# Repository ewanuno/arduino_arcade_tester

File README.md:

this is a simple arduino project to test arcade redemption ticket dispensers and coin acceptors

its been designed to work with Tong li animation tw-950 coin acceptors and TL-002IV ticket distributors.

it should work with others, but if they use 12v signals then it will probably cook your arduino. 

Max vibe coded it and i helped him to get it working and designed the PCB

the lcd is a generic 1602iic

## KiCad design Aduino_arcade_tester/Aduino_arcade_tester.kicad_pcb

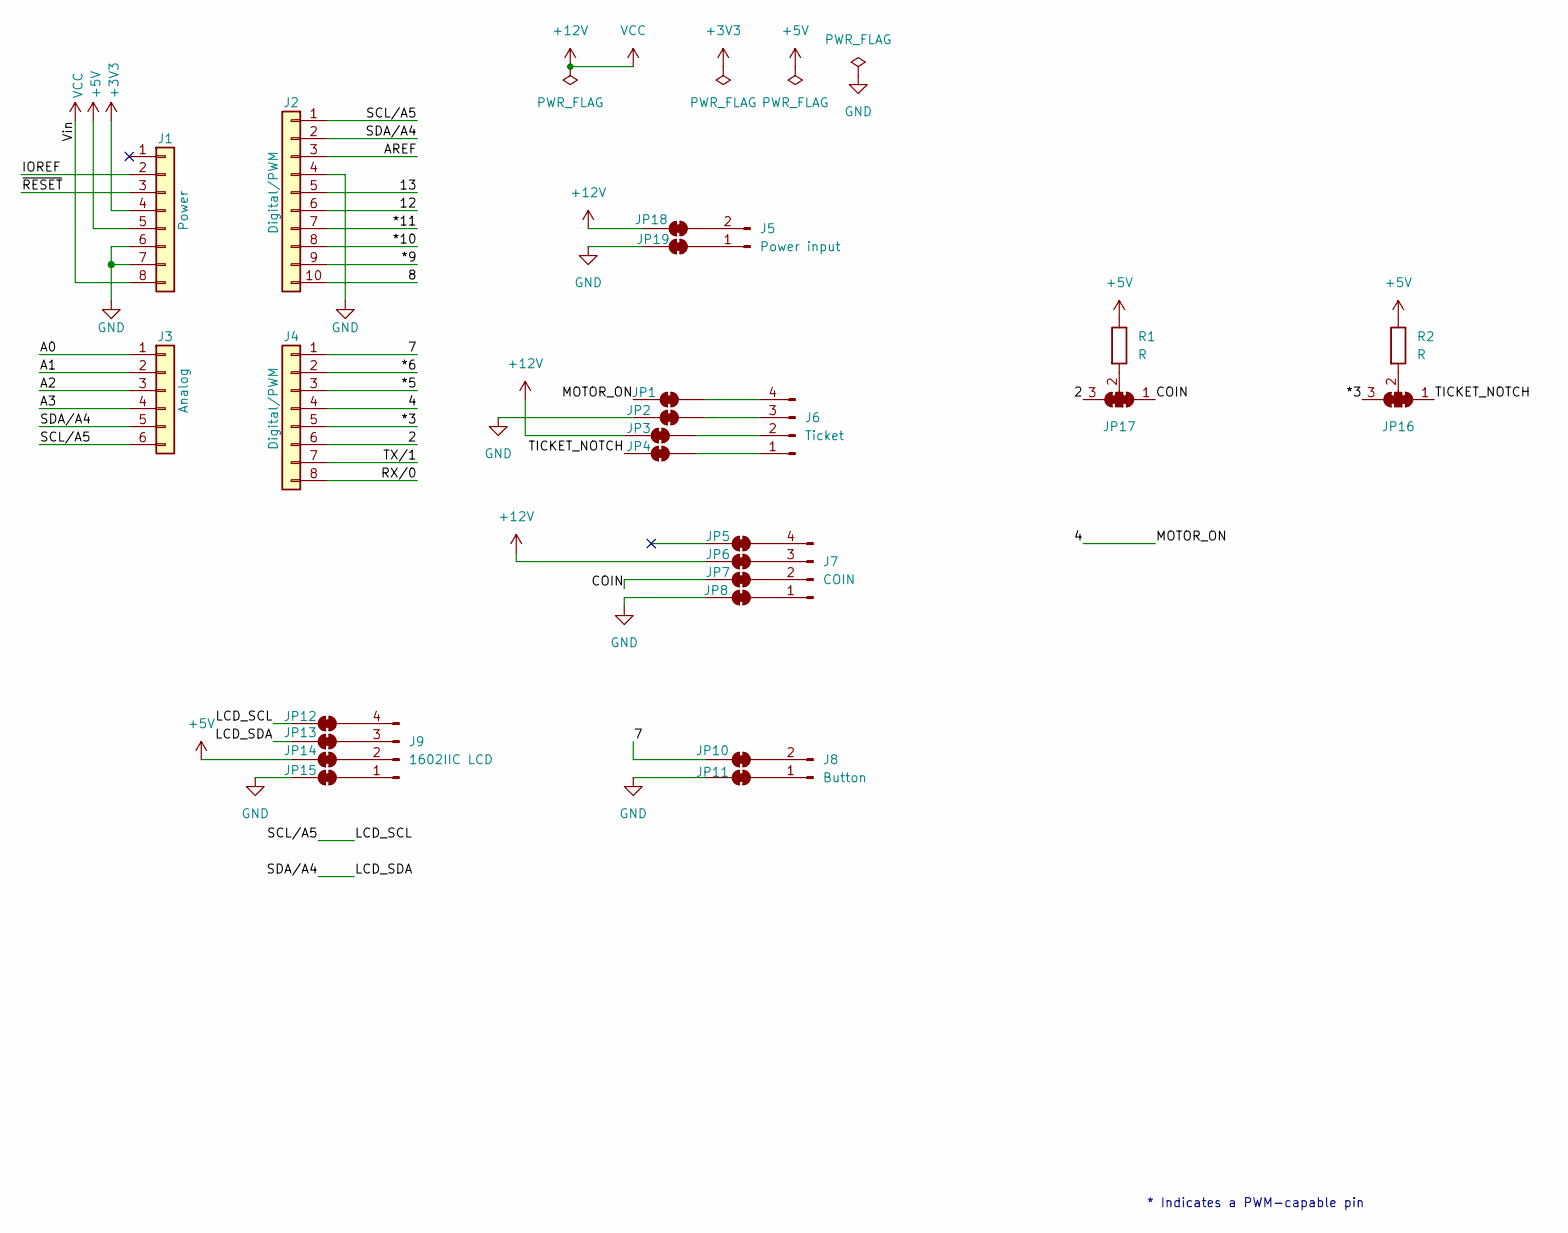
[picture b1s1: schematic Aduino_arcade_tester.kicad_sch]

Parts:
J1: Power; PinSocket_1x08_P2.54mm_Vertical
J2: Digital/PWM; PinSocket_1x10_P2.54mm_Vertical
J3: Analog; PinSocket_1x06_P2.54mm_Vertical
J4: Digital/PWM; PinSocket_1x08_P2.54mm_Vertical
J5: Power input; TerminalBlock_Phoenix_MKDS-1,5-2_1x02_P5.00mm_Horizontal
J6: Ticket; TerminalBlock_Phoenix_MKDS-1,5-4_1x04_P5.00mm_Horizontal
J7: COIN; TerminalBlock_Phoenix_MKDS-1,5-4_1x04_P5.00mm_Horizontal
J8: Button; TerminalBlock_Phoenix_MKDS-1,5-2_1x02_P5.00mm_Horizontal
J9: 1602IIC LCD; PinHeader_1x04_P2.54mm_Vertical
JP1, JP2, JP3, JP4, JP5, JP6, JP7, JP8, JP10, JP11, JP12, JP13, JP14, JP15, JP18, JP19: SolderJumper_2_Bridged; SolderJumper-2_P1.3mm_Bridged_RoundedPad1.0x1.5mm
JP16, JP17: SolderJumper_3_Bridged123; SolderJumper-3_P1.3mm_Bridged123_RoundedPad1.0x1.5mm_Number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
R1, R2: R; R_Axial_DIN0204_L3.6mm_D1.6mm_P5.08mm_Horizontal

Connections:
+3V3: J1.4
+5V: J1.5, JP14.1 (A), R1.1, R2.1
+12V: J1.8, JP3.1 (A), JP6.1 (A), JP18.1 (A)
/2: J4.6, JP17.3 (B)
/4: J4.4, JP1.1 (A)
/7: J4.1, JP10.1 (A)
/8: J2.10
/12: J2.6
/13: J2.5
/*3: J4.5, JP16.3 (B)
/*5: J4.3
/*6: J4.2
/*9: J2.9
/*10: J2.8
/*11: J2.7
/A0: J3.1
/A1: J3.2
/A2: J3.3
/A3: J3.4
/AREF: J2.3
/COIN: JP7.1 (A), JP17.1 (A)
/IOREF: J1.2
/LCD_SCL: J2.1, J3.6, JP12.1 (A)
/LCD_SDA: J2.2, J3.5, JP13.1 (A)
/RX/0: J4.8
/TICKET_NOTCH: JP4.1 (A), JP16.1 (A)
/TX/1: J4.7
/~RESET: J1.3
GND: J1.6, J1.7, J2.4, JP2.1 (A), JP8.1 (A), JP11.1 (A), JP15.1 (A), JP19.1 (A)
unnamed: J5.1, JP19.2 (B)
unnamed: J5.2, JP18.2 (B)
unnamed: J6.1, JP4.2 (B)
unnamed: J6.2, JP3.2 (B)
unnamed: J6.3, JP2.2 (B)
unnamed: J6.4, JP1.2 (B)
unnamed: J7.1, JP8.2 (B)
unnamed: J7.2, JP7.2 (B)
unnamed: J7.3, JP6.2 (B)
unnamed: J7.4, JP5.2 (B_2)
unnamed: J8.1, JP11.2 (B)
unnamed: J8.2, JP10.2 (B)
unnamed: J9.1, JP15.2 (B)
unnamed: J9.2, JP14.2 (B)
unnamed: J9.3, JP13.2 (B)
unnamed: J9.4, JP12.2 (B)
unnamed: JP16.2 (C), R2.2
unnamed: JP17.2 (C), R1.2

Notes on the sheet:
* Indicates a PWM-capable pin

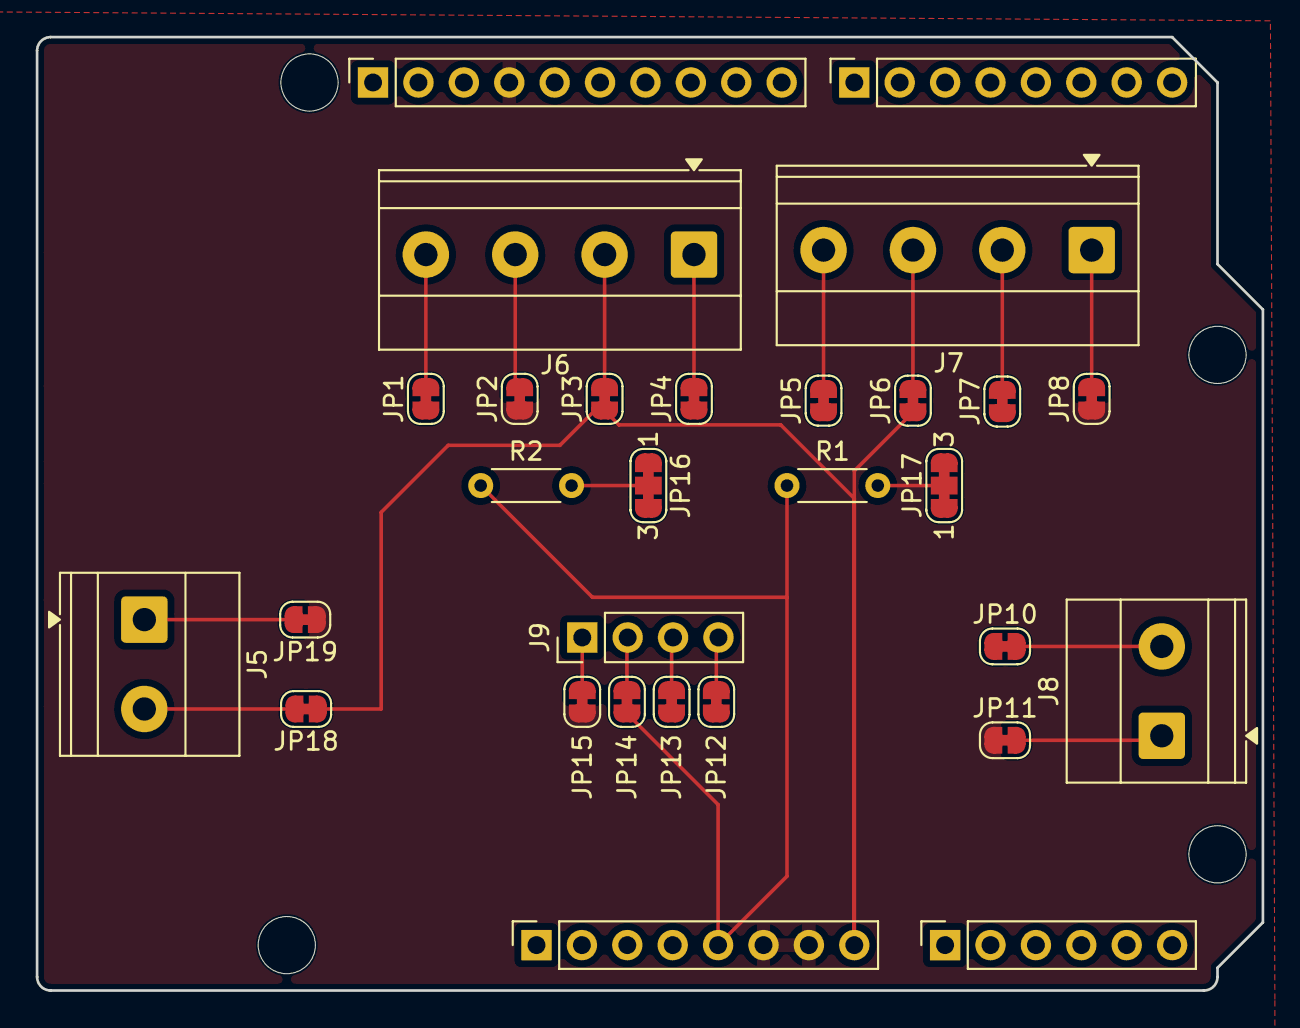
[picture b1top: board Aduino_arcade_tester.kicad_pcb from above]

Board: 2 copper layers, 68.6 x 53.3 mm, 33 parts (0 on the bottom side), 29 nets.

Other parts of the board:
MH1, MH2, MH3, MH4: MountingHole_3.2mm
